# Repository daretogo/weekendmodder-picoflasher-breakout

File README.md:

# weekendmodder-picoflasher-breakout
Repo to home open source files for the PicoFlasher breakout board made with  [@ShawMerlin](https://github.com/ShawMerlin?tab=repositories)

Code for this project is located - https://github.com/X360Tools/PicoFlasher

This board is currently in prototyping phase.  More details to come.

V1.4 has been created and fixes the colors pinouts to match JST Cable color cables.

GNU General Public License v3.0  (Free for use)

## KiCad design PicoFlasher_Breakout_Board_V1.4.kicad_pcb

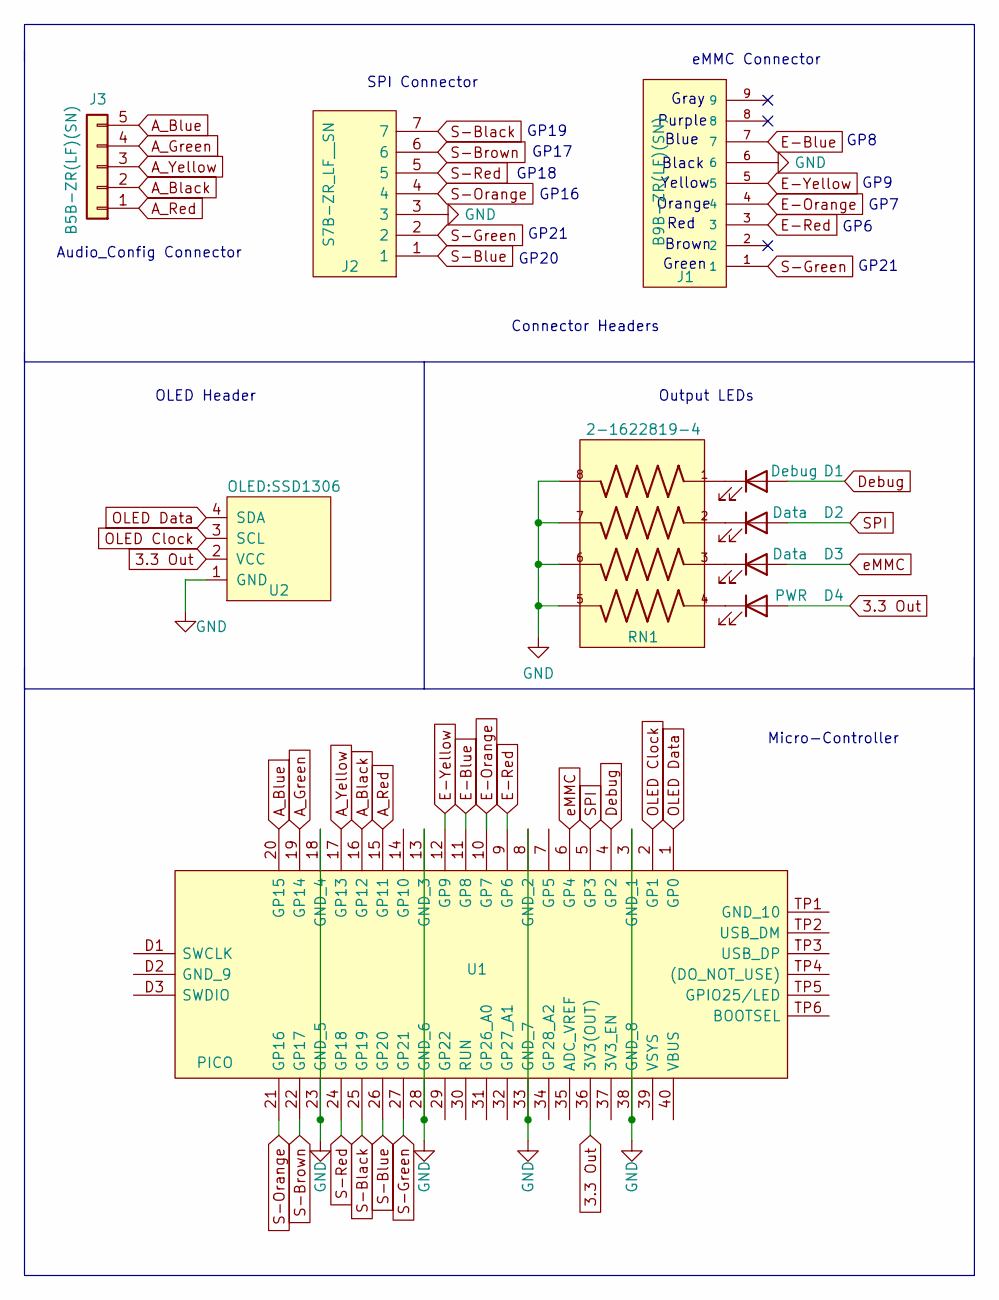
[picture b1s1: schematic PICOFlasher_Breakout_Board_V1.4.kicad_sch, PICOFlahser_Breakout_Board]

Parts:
D1: Debug; LED_0805_2012Metric_Pad1.15x1.40mm_HandSolder
D2, D3: Data; LED_0805_2012Metric_Pad1.15x1.40mm_HandSolder
D4: PWR; LED_0805_2012Metric_Pad1.15x1.40mm_HandSolder
J1: B9B-ZR(LF)(SN); JST_B9B-ZR(LF)(SN)
J2: S7B-ZR_LF__SN; S7BZRLFSN; Manufacturer_Part_Number S7B-ZR(LF)(SN)
J3: B5B-ZR(LF)(SN); JST_B5B-ZR(LF)(SN)
RN1: 2-1622819-4; R_Array_Convex_4x0603
U1: PICO; PICO_THT; Manufacturer_Part_Number PICO
U2: OLED:SSD1306; 128x64OLED

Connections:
3.3 Out: D4.2 (A), U1.36 (3V3(OUT)), U2.2 (VCC); also elsewhere on the board
A_Black: J3.2, U1.16 (GP12); also elsewhere on the board
A_Blue: J3.5, U1.20 (GP15); also elsewhere on the board
A_Green: J3.4, U1.19 (GP14); also elsewhere on the board
A_Red: J3.1, U1.15 (GP11); also elsewhere on the board
A_Yellow: J3.3, U1.17 (GP13); also elsewhere on the board
Debug: D1.2 (A), U1.4 (GP2); also elsewhere on the board
E-Blue: J1.7, U1.11 (GP8); also elsewhere on the board
E-Orange: J1.4, U1.10 (GP7); also elsewhere on the board
E-Red: J1.3, U1.9 (GP6); also elsewhere on the board
E-Yellow: J1.5, U1.12 (GP9); also elsewhere on the board
GND: J1.6, J2.3, RN1.5, RN1.6, RN1.7, RN1.8, U1.3 (GND_1), U1.8 (GND_2), U1.13 (GND_3), U1.18 (GND_4), U1.23 (GND_5), U1.28 (GND_6), U1.33 (GND_7), U1.38 (GND_8), U2.1 (GND); also elsewhere on the board
unnamed: D1.1 (K), RN1.1
unnamed: D2.1 (K), RN1.2
unnamed: D3.1 (K), RN1.3
unnamed: D4.1 (K), RN1.4
OLED Clock: U1.2 (GP1), U2.3 (SCL); also elsewhere on the board
OLED Data: U1.1 (GP0), U2.4 (SDA); also elsewhere on the board
S-Black: J2.7, U1.25 (GP19); also elsewhere on the board
S-Blue: J2.1, U1.26 (GP20); also elsewhere on the board
S-Brown: J2.6, U1.22 (GP17); also elsewhere on the board
S-Green: J1.1, J2.2, U1.27 (GP21)
S-Orange: J2.4, U1.21 (GP16); also elsewhere on the board
S-Red: J2.5, U1.24 (GP18); also elsewhere on the board
SPI: D2.2 (A), U1.5 (GP3); also elsewhere on the board
eMMC: D3.2 (A), U1.6 (GP4); also elsewhere on the board

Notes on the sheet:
Yellow
Brown
GP16
GP21
GP17
Gray
Micro-Controller
GP8
Red
Audio_Config Connector
Connector Headers
Black
OLED Header
Output LEDs
GP20
GP18
GP7
Blue
Green
Purple
eMMC Connector
Orange
GP19
GP9
SPI Connector
GP6

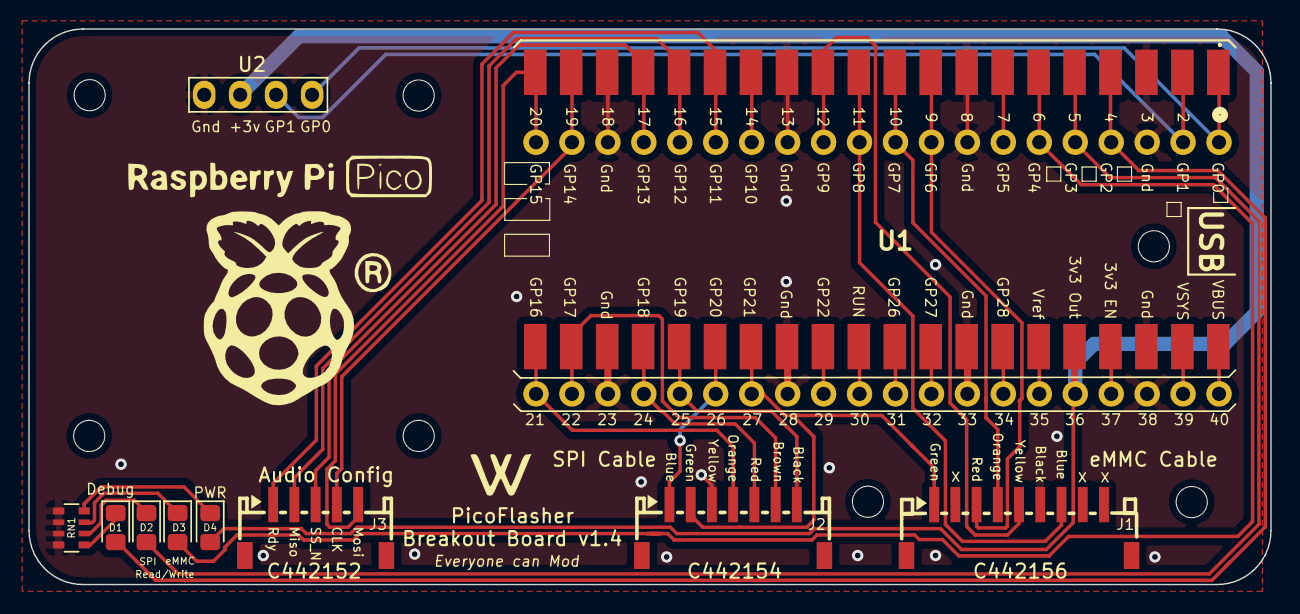
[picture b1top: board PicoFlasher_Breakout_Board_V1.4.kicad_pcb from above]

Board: 2 copper layers, 87.8 x 39.2 mm, 11 parts (0 on the bottom side), 26 nets.

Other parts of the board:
U1e: PICO; PICO_SMD

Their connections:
3.3 Out: U1e.36 (3V3(OUT)); also elsewhere on the board
A_Black: U1e.16 (GP12); also elsewhere on the board
A_Blue: U1e.20 (GP15); also elsewhere on the board
A_Green: U1e.19 (GP14); also elsewhere on the board
A_Red: U1e.15 (GP11); also elsewhere on the board
A_Yellow: U1e.17 (GP13); also elsewhere on the board
Debug: U1e.4 (GP2); also elsewhere on the board
E-Blue: U1e.11 (GP8); also elsewhere on the board
E-Orange: U1e.10 (GP7); also elsewhere on the board
E-Red: U1e.9 (GP6); also elsewhere on the board
E-Yellow: U1e.12 (GP9); also elsewhere on the board
GND: U1e.3 (GND_1), U1e.8 (GND_2), U1e.13 (GND_3), U1e.18 (GND_4), U1e.23 (GND_5), U1e.28 (GND_6), U1e.33 (GND_7), U1e.38 (GND_8); also elsewhere on the board
OLED Clock: U1e.2 (GP1); also elsewhere on the board
OLED Data: U1e.1 (GP0); also elsewhere on the board
S-Black: U1e.25 (GP19); also elsewhere on the board
S-Blue: U1e.26 (GP20); also elsewhere on the board
S-Brown: U1e.22 (GP17); also elsewhere on the board
S-Orange: U1e.21 (GP16); also elsewhere on the board
S-Red: U1e.24 (GP18); also elsewhere on the board
SPI: U1e.5 (GP3); also elsewhere on the board
eMMC: U1e.6 (GP4); also elsewhere on the board

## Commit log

2022-03-14 Create LICENSE
